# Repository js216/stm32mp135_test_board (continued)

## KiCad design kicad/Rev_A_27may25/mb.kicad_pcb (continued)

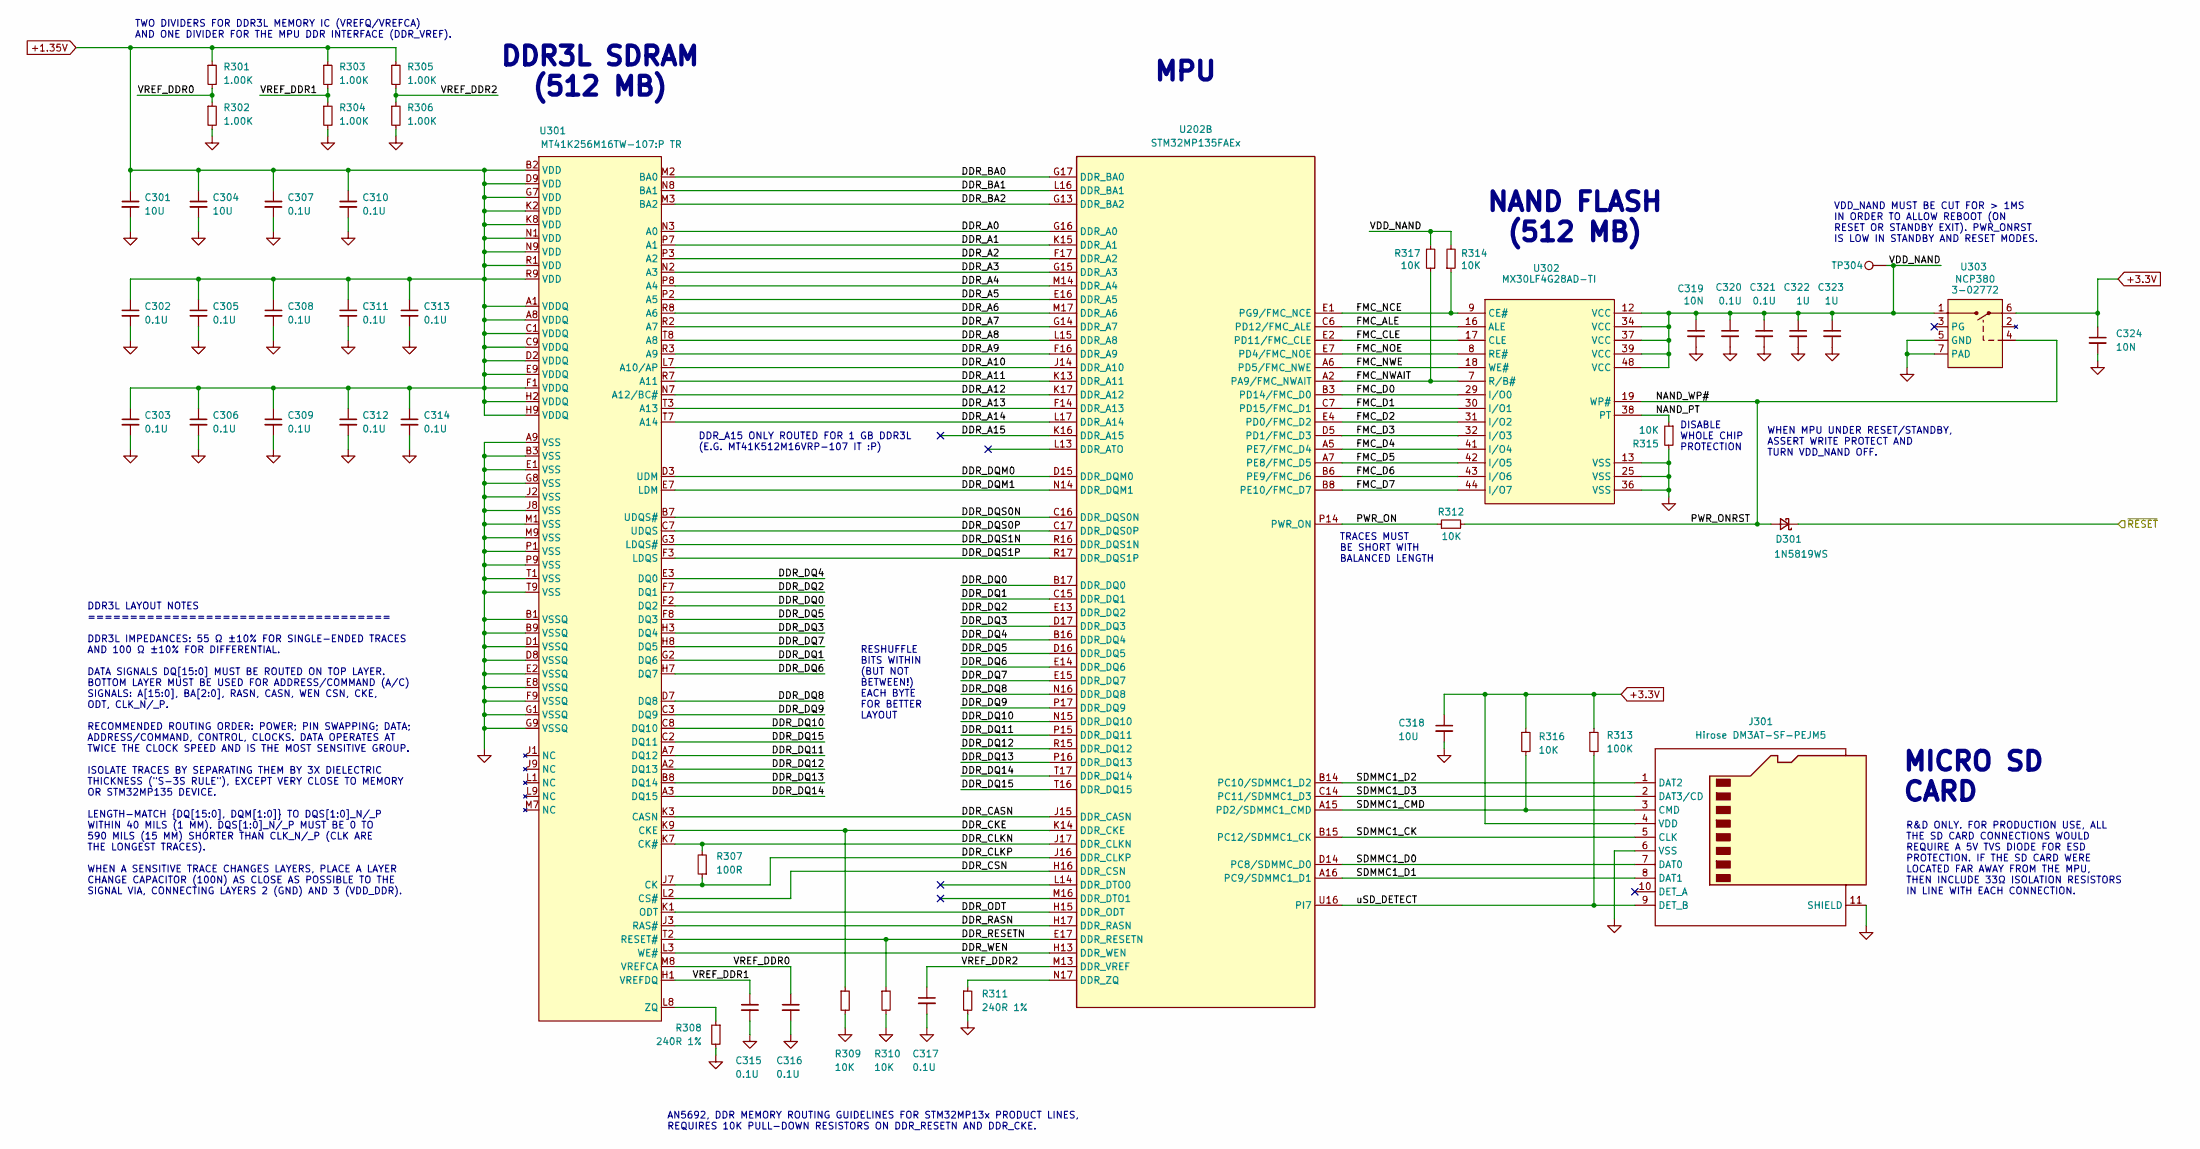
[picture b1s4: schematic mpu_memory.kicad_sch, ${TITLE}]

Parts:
C301, C304, C318: 10U; C_0402_1005Metric; JLCPCB C15525
C302, C303, C305, C306, C307, C308, C309, C310, C311, C312, C313, C314, C315, C316, C317, C320, C321: 0.1U; C_0402_1005Metric; JLCPCB C307331
C319, C324: 10N; C_0402_1005Metric; JLCPCB C15195
C322, C323: 1U; C_0402_1005Metric; JLCPCB C52923
D301: 1N5819WS; D_SOD-323; JLCPCB C191023
J301: Hirose DM3AT-SF-PEJM5; microSD_HC_Hirose_DM3AT-SF-PEJM5; JLCPCB C114218
R301, R302, R303, R304, R305, R306: 1.00K; R_0402_1005Metric; JLCPCB C11702
R307: 100R; R_0402_1005Metric; JLCPCB C25076
R308, R311: 240R 1%; R_0402_1005Metric; JLCPCB C25094
R309, R310, R312, R314, R315, R316, R317: 10K; R_0402_1005Metric; JLCPCB C25744
R313: 100K; R_0402_1005Metric; JLCPCB C25741
TP304: Keystone 5005 (red); TestPoint_Pad_D1.0mm
U202: STM32MP135FAEx; LFBGA-289_14x14mm_Layout17x17_P0.8mm; JLCPCB C7501745
U301: MT41K256M16TW-107:P TR; Micron_FBGA-96_8x14mm_Layout9x16_P0.8mm; JLCPCB C253882
U302: MX30LF4G28AD-TI; TSOP-I-48_18.4x12mm_P0.5mm; JLCPCB C2894351
U303: NCP380; DFN-6-1EP_2x2mm_P0.65mm_EP1x1.6mm; JLCPCB C145185

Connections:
+1.35V: C301.1, C302.1, C303.1, C304.1, C305.1, C306.1, C307.1, C308.1, C309.1, C310.1, C311.1, C312.1, C313.1, C314.1, R301.1, R303.1, R305.1, U301.A1 (VDDQ), U301.A8 (VDDQ), U301.B2 (VDD), U301.C1 (VDDQ), U301.C9 (VDDQ), U301.D2 (VDDQ), U301.D9 (VDD), U301.E9 (VDDQ), U301.F1 (VDDQ), U301.G7 (VDD), U301.H2 (VDDQ), U301.H9 (VDDQ), U301.K2 (VDD), U301.K8 (VDD), U301.N1 (VDD), U301.N9 (VDD), U301.R1 (VDD), U301.R9 (VDD); also elsewhere on the board
+3.3V: C318.1, C324.1, J301.4 (VDD), R313.1, R316.1, U303.6; also elsewhere on the board
/MPU Memory/DDR_A0: U202.G16 (DDR_A0), U301.N3 (A0)
/MPU Memory/DDR_A1: U202.K15 (DDR_A1), U301.P7 (A1)
/MPU Memory/DDR_A2: U202.F17 (DDR_A2), U301.P3 (A2)
/MPU Memory/DDR_A3: U202.G15 (DDR_A3), U301.N2 (A3)
/MPU Memory/DDR_A4: U202.M14 (DDR_A4), U301.P8 (A4)
/MPU Memory/DDR_A5: U202.E16 (DDR_A5), U301.P2 (A5)
/MPU Memory/DDR_A6: U202.M17 (DDR_A6), U301.R8 (A6)
/MPU Memory/DDR_A7: U202.G14 (DDR_A7), U301.R2 (A7)
/MPU Memory/DDR_A8: U202.L15 (DDR_A8), U301.T8 (A8)
/MPU Memory/DDR_A9: U202.F16 (DDR_A9), U301.R3 (A9)
/MPU Memory/DDR_A10: U202.J14 (DDR_A10), U301.L7 (A10/AP)
/MPU Memory/DDR_A11: U202.K13 (DDR_A11), U301.R7 (A11)
/MPU Memory/DDR_A12: U202.K17 (DDR_A12), U301.N7 (A12/BC#)
/MPU Memory/DDR_A13: U202.F14 (DDR_A13), U301.T3 (A13)
/MPU Memory/DDR_A14: U202.L17 (DDR_A14), U301.T7 (A14)
/MPU Memory/DDR_A15: U202.K16 (DDR_A15)
/MPU Memory/DDR_BA0: U202.G17 (DDR_BA0), U301.M2 (BA0)
/MPU Memory/DDR_BA1: U202.L16 (DDR_BA1), U301.N8 (BA1)
/MPU Memory/DDR_BA2: U202.G13 (DDR_BA2), U301.M3 (BA2)
/MPU Memory/DDR_CASN: U202.J15 (DDR_CASN), U301.K3 (CASN)
/MPU Memory/DDR_CKE: R309.1, U202.K14 (DDR_CKE), U301.K9 (CKE)
/MPU Memory/DDR_CLKN: R307.2, U202.J17 (DDR_CLKN), U301.K7 (CK#)
/MPU Memory/DDR_CLKP: R307.1, U202.J16 (DDR_CLKP), U301.J7 (CK)
/MPU Memory/DDR_CSN: U202.H16 (DDR_CSN), U301.L2 (CS#)
/MPU Memory/DDR_DQ0: U202.B17 (DDR_DQ0), U301.F2 (DQ2)
/MPU Memory/DDR_DQ1: U202.C15 (DDR_DQ1), U301.G2 (DQ6)
/MPU Memory/DDR_DQ2: U202.E13 (DDR_DQ2), U301.F7 (DQ1)
/MPU Memory/DDR_DQ3: U202.D17 (DDR_DQ3), U301.H3 (DQ4)
/MPU Memory/DDR_DQ4: U202.B16 (DDR_DQ4), U301.E3 (DQ0)
/MPU Memory/DDR_DQ5: U202.D16 (DDR_DQ5), U301.F8 (DQ3)
/MPU Memory/DDR_DQ6: U202.E14 (DDR_DQ6), U301.H7 (DQ7)
/MPU Memory/DDR_DQ7: U202.E15 (DDR_DQ7), U301.H8 (DQ5)
/MPU Memory/DDR_DQ8: U202.N16 (DDR_DQ8), U301.D7 (DQ8)
/MPU Memory/DDR_DQ9: U202.P17 (DDR_DQ9), U301.C3 (DQ9)
/MPU Memory/DDR_DQ10: U202.N15 (DDR_DQ10), U301.C8 (DQ10)
/MPU Memory/DDR_DQ11: U202.P15 (DDR_DQ11), U301.A7 (DQ12)
/MPU Memory/DDR_DQ12: U202.R15 (DDR_DQ12), U301.A2 (DQ13)
/MPU Memory/DDR_DQ13: U202.P16 (DDR_DQ13), U301.B8 (DQ14)
/MPU Memory/DDR_DQ14: U202.T17 (DDR_DQ14), U301.A3 (DQ15)
/MPU Memory/DDR_DQ15: U202.T16 (DDR_DQ15), U301.C2 (DQ11)
/MPU Memory/DDR_DQM0: U202.D15 (DDR_DQM0), U301.D3 (UDM)
/MPU Memory/DDR_DQM1: U202.N14 (DDR_DQM1), U301.E7 (LDM)
/MPU Memory/DDR_DQS0N: U202.C16 (DDR_DQS0N), U301.B7 (UDQS#)
/MPU Memory/DDR_DQS0P: U202.C17 (DDR_DQS0P), U301.C7 (UDQS)
/MPU Memory/DDR_DQS1N: U202.R16 (DDR_DQS1N), U301.G3 (LDQS#)
/MPU Memory/DDR_DQS1P: U202.R17 (DDR_DQS1P), U301.F3 (LDQS)
/MPU Memory/DDR_ODT: U202.H15 (DDR_ODT), U301.K1 (ODT)
/MPU Memory/DDR_RASN: U202.H17 (DDR_RASN), U301.J3 (RAS#)
/MPU Memory/DDR_RESETN: R310.1, U202.E17 (DDR_RESETN), U301.T2 (RESET#)
/MPU Memory/DDR_WEN: U202.H13 (DDR_WEN), U301.L3 (WE#)
/MPU Memory/FMC_ALE: U202.C6 (PD12/FMC_ALE), U302.16 (ALE)
/MPU Memory/FMC_CLE: U202.E2 (PD11/FMC_CLE), U302.17 (CLE)
/MPU Memory/FMC_D0: U202.B3 (PD14/FMC_D0), U302.29 (I/O0)
/MPU Memory/FMC_D1: U202.C7 (PD15/FMC_D1), U302.30 (I/O1)
/MPU Memory/FMC_D2: U202.E4 (PD0/FMC_D2), U302.31 (I/O2)
/MPU Memory/FMC_D3: U202.D5 (PD1/FMC_D3), U302.32 (I/O3)
/MPU Memory/FMC_D4: U202.A5 (PE7/FMC_D4), U302.41 (I/O4)
/MPU Memory/FMC_D5: U202.A7 (PE8/FMC_D5), U302.42 (I/O5)
/MPU Memory/FMC_D6: U202.B6 (PE9/FMC_D6), U302.43 (I/O6)
/MPU Memory/FMC_D7: U202.B8 (PE10/FMC_D7), U302.44 (I/O7)
/MPU Memory/FMC_NCE: R314.1, U202.E1 (PG9/FMC_NCE), U302.9 (CE#)
/MPU Memory/FMC_NOE: U202.E7 (PD4/FMC_NOE), U302.8 (RE#)
/MPU Memory/FMC_NWAIT: R317.1, U202.A2 (PA9/FMC_NWAIT), U302.7 (R/B#)
/MPU Memory/FMC_NWE: U202.A6 (PD5/FMC_NWE), U302.18 (WE#)
/MPU Memory/NAND_PT: R315.1, U302.38 (PT)
/MPU Memory/NAND_WP#: D301.2 (A), R312.2, U302.19 (WP#), U303.4
/MPU Memory/PWR_ON: R312.1, U202.P14 (PWR_ON)
/MPU Memory/SDMMC1_CK: J301.5 (CLK), U202.B15 (PC12/SDMMC1_CK)
/MPU Memory/SDMMC1_CMD: J301.3 (CMD), R316.2, U202.A15 (PD2/SDMMC1_CMD)
/MPU Memory/SDMMC1_D0: J301.7 (DAT0), U202.D14 (PC8/SDMMC_D0)
/MPU Memory/SDMMC1_D1: J301.8 (DAT1), U202.A16 (PC9/SDMMC1_D1)
/MPU Memory/SDMMC1_D2: J301.1 (DAT2), U202.B14 (PC10/SDMMC1_D2)
/MPU Memory/SDMMC1_D3: J301.2 (DAT3/CD), U202.C14 (PC11/SDMMC1_D3)
/MPU Memory/VDD_NAND: C319.1, C320.1, C321.1, C322.1, C323.1, R314.2, R317.2, TP304.1, U302.12 (VCC), U302.34 (VCC), U302.37 (VCC), U302.39 (VCC), U302.48 (VCC), U303.1
/MPU Memory/VREF_DDR0: C316.1, R301.2, R302.1, U301.M8 (VREFCA)
/MPU Memory/VREF_DDR1: C315.1, R303.2, R304.1, U301.H1 (VREFDQ)
/MPU Memory/VREF_DDR2: C317.1, R305.2, R306.1, U202.M13 (DDR_VREF)
/MPU Memory/uSD_DETECT: J301.9 (DET_B), R313.2, U202.U16 (PI7)
/~RESET: D301.1 (K); also elsewhere on the board
GND: C301.2, C302.2, C303.2, C304.2, C305.2, C306.2, C307.2, C308.2, C309.2, C310.2, C311.2, C312.2, C313.2, C314.2, C315.2, C316.2, C317.2, C318.2, C319.2, C320.2, C321.2, C322.2, C323.2, C324.2, J301.6 (VSS), J301.11 (SHIELD), R302.2, R304.2, R306.2, R308.2, R309.2, R310.2, R311.2, R315.2, U301.A9 (VSS), U301.B1 (VSSQ), U301.B3 (VSS), U301.B9 (VSSQ), U301.D1 (VSSQ), U301.D8 (VSSQ), U301.E1 (VSS), U301.E2 (VSSQ), U301.E8 (VSSQ), U301.F9 (VSSQ), U301.G1 (VSSQ), U301.G8 (VSS), U301.G9 (VSSQ), U301.J2 (VSS), U301.J8 (VSS), U301.M1 (VSS), U301.M9 (VSS), U301.P1 (VSS), U301.P9 (VSS), U301.T1 (VSS), U301.T9 (VSS), U302.13 (VSS), U302.25 (VSS), U302.36 (VSS), U303.5 (GND), U303.7 (PAD); also elsewhere on the board
unnamed: R311.1, U202.N17 (DDR_ZQ)
unnamed: R308.1, U301.L8 (ZQ)

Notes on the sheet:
MICRO SD CARD
DDR3L SDRAM (512 MB)
VDD_NAND MUST BE CUT FOR > 1MS IN ORDER TO ALLOW REBOOT (ON RESET OR STANDBY EXIT). PWR_ONRST IS LOW IN STANDBY AND RESET MODES.
DDR_A15 ONLY ROUTED FOR 1 GB DDR3L (E.G. MT41K512M16VRP-107 IT :P)
TWO DIVIDERS FOR DDR3L MEMORY IC (VREFQ/VREFCA) AND ONE DIVIDER FOR THE MPU DDR INTERFACE (DDR_VREF).
MPU
AN5692, DDR MEMORY ROUTING GUIDELINES FOR STM32MP13x PRODUCT LINES, REQUIRES 10K PULL-DOWN RESISTORS ON DDR_RESETN AND DDR_CKE.
TRACES MUST BE SHORT WITH BALANCED LENGTH
WHEN MPU UNDER RESET/STANDBY, ASSERT WRITE PROTECT AND TURN VDD_NAND OFF.
RESHUFFLE BITS WITHIN (BUT NOT BETWEEN!) EACH BYTE FOR BETTER LAYOUT
NAND FLASH (512 MB)
DISABLE WHOLE CHIP PROTECTION
DDR3L LAYOUT NOTES ==================================== DDR3L IMPEDANCES: 55 Ω ±10% FOR SINGLE-ENDED TRACES AND 100 Ω ±10% FOR DIFFERENTIAL. DATA SIGNALS DQ[15:0] MUST BE ROUTED ON TOP LAYER. BOTTOM LAYER MUST BE USED FOR ADDRESS/COMMAND (A/C) SIGNALS: A[15:0], BA[2:0], RASN, CASN, WEN CSN, CKE, OD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
R&D ONLY. FOR PRODUCTION USE, ALL THE SD CARD CONNECTIONS WOULD REQUIRE A 5V TVS DIODE FOR ESD PROTECTION. IF THE SD CARD WERE LOCATED FAR AWAY FROM THE MPU, THEN INCLUDE 33Ω ISOLATION RESISTORS IN LINE WITH EACH CONNECTION.

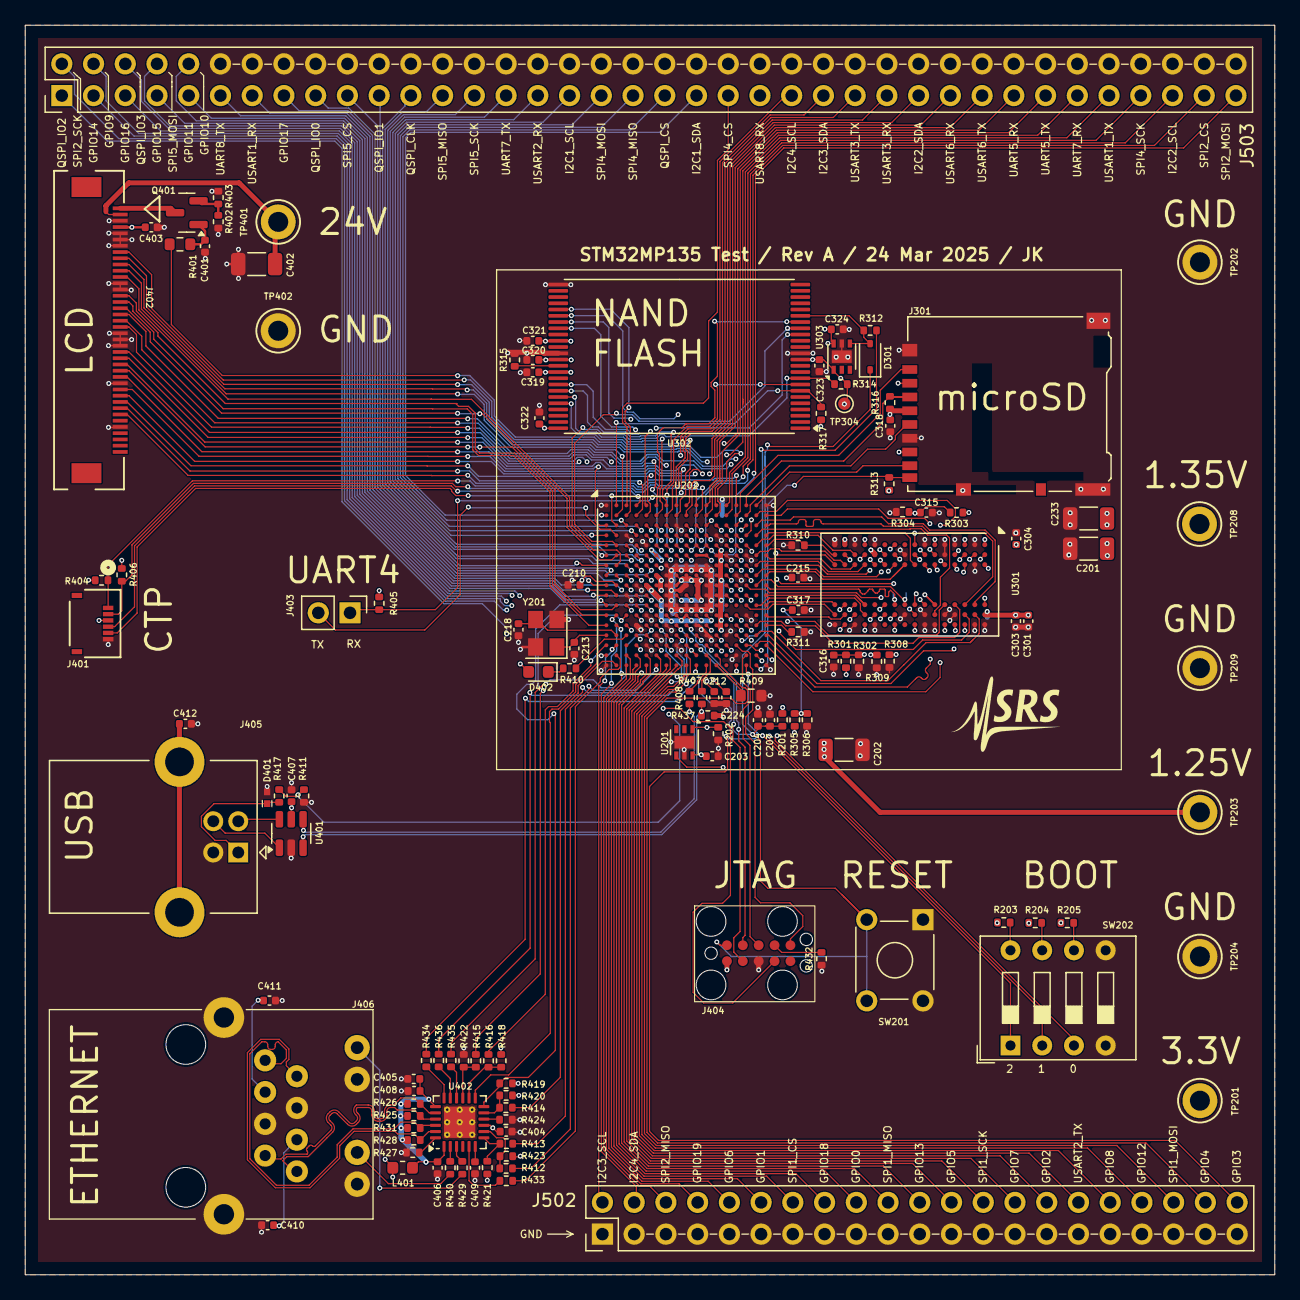
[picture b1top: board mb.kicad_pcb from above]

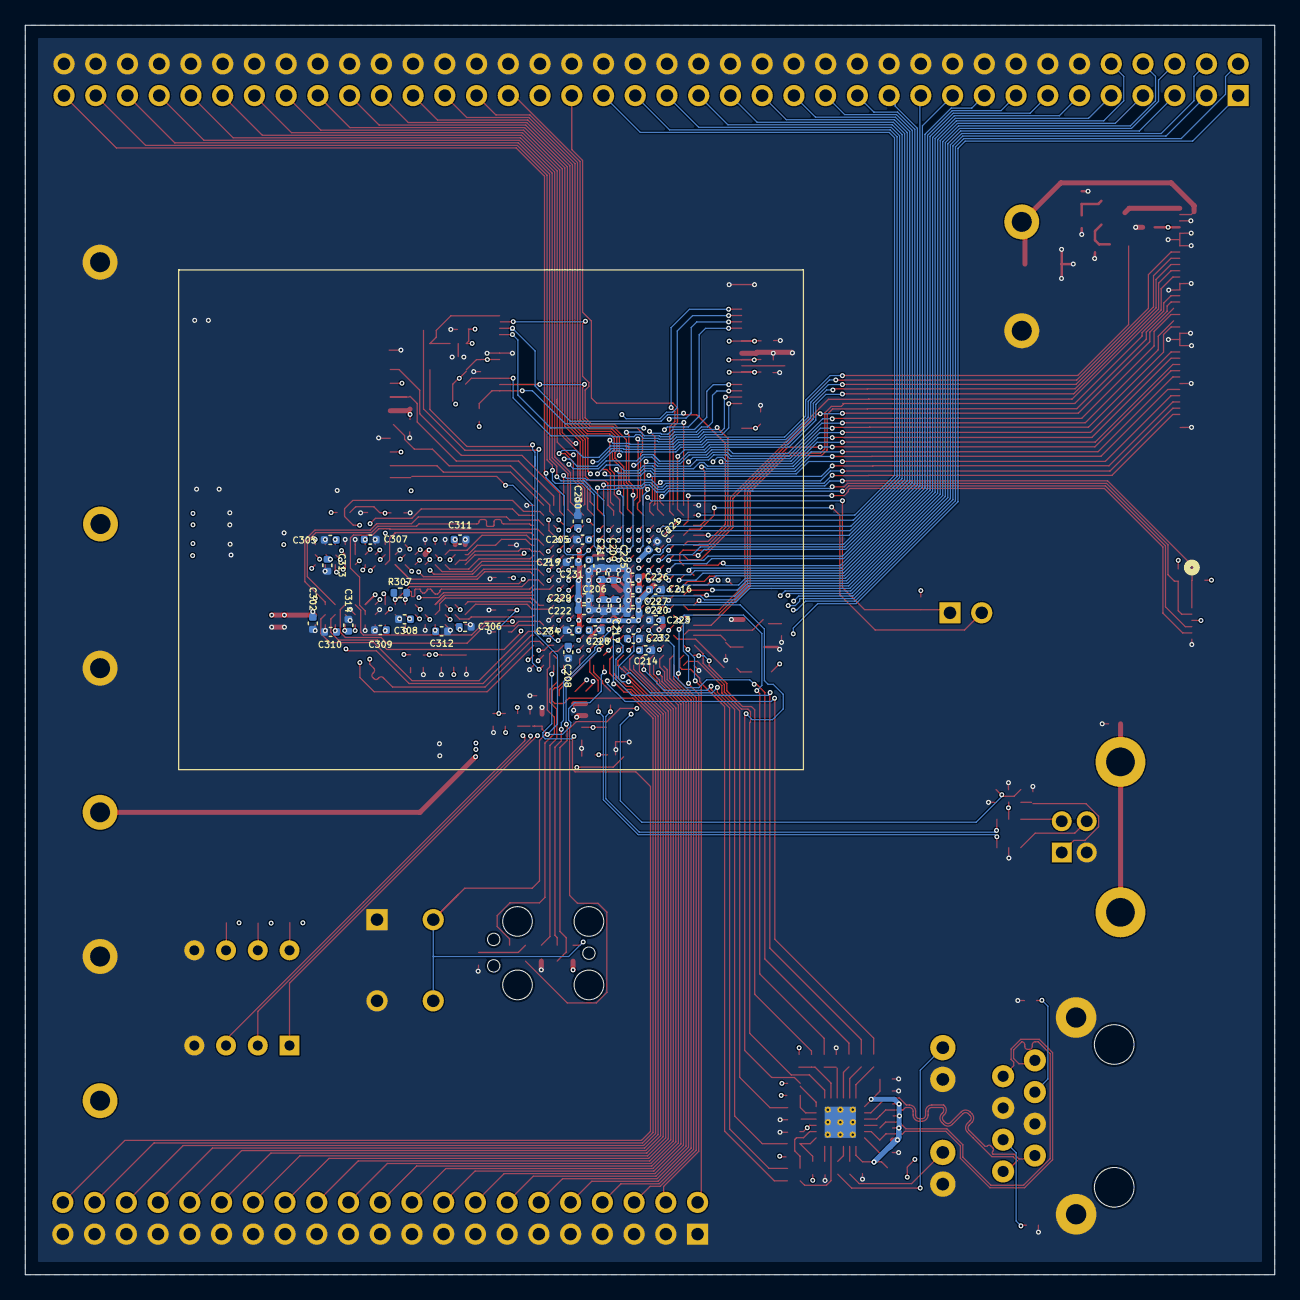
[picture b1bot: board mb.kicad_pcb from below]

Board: 6 copper layers, 100.0 x 100.0 mm, 162 parts (34 on the bottom side), 243 nets.

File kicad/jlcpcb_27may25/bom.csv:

"Reference","Value","Qty","JLCPCB"
"C201","100U","1","C15008"
"C202","100U","1","C15008"
"C203","10N","1","C15195"
"C204","10N","1","C15195"
"C205","1U","1","C52923"
"C206","1U","1","C52923"
"C207","1U","1","C52923"
"C208","1U","1","C52923"
"C209","1U","1","C52923"
"C210","1U","1","C52923"
"C211","1U","1","C52923"
"C212","1U","1","C52923"
"C213","10P","1","C32949"
"C214","1U","1","C52923"
"C215","1U","1","C52923"
"C216","1U","1","C52923"
"C217","1U","1","C52923"
"C218","10P","1","C32949"
"C219","1U","1","C52923"
"C220","1U","1","C52923"
"C221","1U","1","C52923"
"C222","1nF","1","C1523"
"C223","1U","1","C52923"
"C224","2.2U","1"," C12530"
"C225","1U","1","C52923"
"C226","1nF","1","C1523"
"C227","1U","1","C52923"
"C228","2.2U","1"," C12530"
"C229","1U","1","C52923"
"C230","1U","1","C52923"
"C231","0.1U","1","C307331"
"C232","1U","1","C52923"
"C233","100U","1","C15008"
"C234","1U","1","C52923"
"C301","10U","1","C15525"
"C302","0.1U","1","C307331"
"C303","0.1U","1","C307331"
"C304","10U","1","C15525"
"C305","0.1U","1","C307331"
"C306","0.1U","1","C307331"
"C307","0.1U","1","C307331"
"C308","0.1U","1","C307331"
"C309","0.1U","1","C307331"
"C310","0.1U","1","C307331"
"C311","0.1U","1","C307331"
"C312","0.1U","1","C307331"
"C313","0.1U","1","C307331"
"C314","0.1U","1","C307331"
"C315","0.1U","1","C307331"
"C316","0.1U","1","C307331"
"C317","0.1U","1","C307331"
"C318","10U","1","C15525"
"C319","10N","1","C15195"
"C320","0.1U","1","C307331"
"C321","0.1U","1","C307331"
"C322","1U","1","C52923"
"C323","1U","1","C52923"
"C324","10N","1","C15195"
"C401","4.7U","1","C23733"
"C402","4.7U 50V","1","C29823"
"C403","0.1U","1","C307331"
"C404","0.1U","1","C307331"
"C405","10U","1","C15525"
"C406","0.1U","1","C307331"
"C407","0.1U","1","C307331"
"C408","0.1U","1","C307331"
"C409","1U","1","C52923"
"C410","0.1U","1","C307331"
"C411","0.1U","1","C307331"
"C412","1nF","1","C1523"
"D301","1N5819WS","1","C191023"
"D401","6V TVS","1","C472589"
"D402","Red","1","C2286"
"J301","Hirose DM3AT-SF-PEJM5","1","C114218"
"J401","Conn_01x08","1","C5213748"
"J402","Molex 541044031","1","C164172"
"J403","Header","1",""
"J405","USB_B","1",""
"J406","J1011F21PNL","1",""
"J502","Conn_02x21_Odd_Even","1",""
"J503","Conn_02x38_Odd_Even","1",""
"L401","600R @ 100MHz","1","C1002"
"Q401"," MMBT5551","1","C2145"
"R201","10K","1","C25744"
"R202","10K","1","C25744"
"R203","1.00K","1","C11702"
"R204","1.00K","1","C11702"
"R205","1.00K","1","C11702"
"R301","1.00K","1","C11702"
"R302","1.00K","1","C11702"
"R303","1.00K","1","C11702"
"R304","1.00K","1","C11702"
"R305","1.00K","1","C11702"
"R306","1.00K","1","C11702"
"R307","100R","1","C25076"
"R308","240R 1%","1","C25094"
"R309","10K","1","C25744"
"R310","10K","1","C25744"
"R311","240R 1%","1","C25094"
"R312","10K","1","C25744"
"R313","100K","1","C25741"
"R314","10K","1","C25744"
"R315","10K","1","C25744"
"R316","10K","1","C25744"
"R317","10K","1","C25744"
"R401","270","1","C22966"
"R402","100R","1","C25076"
"R403","100R","1","C25076"
"R404","10K","1","C25744"
"R405","10K","1","C25744"
"R406","10K","1","C25744"
"R407","30.1","1","C67234"
"R408","30.1","1","C67234"
"R409","3.00K","1","C4211"
"R410","330","1","C25104"
"R411","10K","1","C25744"
"R412","33","1","C25105"
"R413","33","1","C25105"
"R414","33","1","C25105"
"R415","0","1","C17168"
"R416","0","1","C17168"
"R417","10K","1","C25744"
"R418","10K","1","C25744"
"R419","1.5K","1","C25867"
"R420","10K","1","C25744"
"R421","10K","1","C25744"
"R422","10K","1","C25744"
"R423","10K","1","C25744"
"R424","10K","1","C25744"
"R425","49.9","1","C25120"
"R426","49.9","1","C25120"
"R427","12.1K","1","C25852"
"R428","49.9","1","C25120"
"R429","1.00K","1","C11702"
"R430","1.00K","1","C11702"
"R431","49.9","1","C25120"
"R432","10K","1","C25744"
"R433","33","1","C25105"
"R434","0","1","C17168"
"R435","0","1","C17168"
"R436","0","1","C17168"
"R437","1.5K","1","C25867"
"SW201","Omron B3F-1052","1",""
"SW202","SW_DIP_x04","1",""
"U201","NCP380","1","C145185"
"U202","STM32MP135FAEx","1","C7501745"
"U301","MT41K256M16TW-107:P TR","1","C253882 "
"U302","MX30LF4G28AD-TI","1","C2894351"
"U303","NCP380","1","C145185"
"U401","TPD2S017","1","C880115"
"U402","LAN8742A-CZ-TR","1","C621424"
"Y201","24 MHz","1","C70571"

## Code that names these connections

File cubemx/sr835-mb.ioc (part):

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Mcu.Name=STM32MP135FAEx
Mcu.Package=LFBGA289
Mcu.UserName=STM32MP135FAEx
PA0.GPIOParameters=PinAttribute
PA0.PinAttribute=Application
PA0.Signal=S_TIM2_CH1_ETR
PA1.GPIOParameters=GPIO_Label,PinAttribute
PA1.GPIO_Label=uSD_DETECT
PA1.PinAttribute=Free
PA1.Signal=GPIO_Input
PA10.GPIOParameters=GPIO_Label,PinAttribute
PA10.GPIO_Label=GPIO3
PA10.PinAttribute=Free
PA10.Signal=GPIO_Output
PA11.GPIOParameters=PinAttribute
PA11.Mode=ETH Clock Output (PHY without Quartz)
PA11.PinAttribute=Application
PA11.Signal=ETH1_CLK
PA12.GPIOParameters=PinAttribute
PA12.Mode=RGB565
PA12.PinAttribute=Application
PA12.Signal=LTDC_G6
PA13.GPIOParameters=GPIO_Label,PinAttribute
PA13.GPIO_Label=LED_RED
PA13.PinAttribute=Free
PA13.Signal=GPIO_Output
PA14.GPIOParameters=GPIO_Label,PinAttribute
PA14.GPIO_Label=GPIO4
PA14.PinAttribute=Free
PA14.Signal=GPIO_Output
PA15.GPIOParameters=PinAttribute
PA15.Mode=RGB565
PA15.PinAttribute=Application
PA15.Signal=LTDC_G7
PA2.GPIOParameters=PinAttribute
PA2.Mode=IN1-Single-Ended
PA2.PinAttribute=Application
PA2.Signal=ADC1_INP1
PA3.GPIOParameters=PinAttribute
PA3.Mode=Full_Duplex_Master
PA3.PinAttribute=Application
PA3.Signal=SPI1_MOSI
PA4.GPIOParameters=GPIO_Label,PinAttribute
PA4.GPIO_Label=GPIO0
PA4.PinAttribute=Free
PA4.Signal=GPIO_Output
PA5.GPIOParameters=GPIO_Label,PinAttribute
PA5.GPIO_Label=GPIO1
PA5.PinAttribute=Free
PA5.Signal=GPIO_Output
PA6.GPIOParameters=PinAttribute
PA6.Mode=CTS_RTS
PA6.PinAttribute=Application
PA6.Signal=UART4_RTS
PA7.GPIOParameters=PinAttribute
PA7.Mode=RMII (Reduced MII)
PA7.PinAttribute=Application
PA7.Signal=ETH1_CRS_DV
PA8.GPIOParameters=PinAttribute
PA8.Mode=I2C
PA8.PinAttribute=Application
PA8.Signal=I2C4_SDA
PA9.GPIOParameters=PinAttribute
PA9.PinAttribute=Application
PA9.Signal=FMC_NWAIT
PB0.GPIOParameters=PinAttribute
PB0.Mode=CTS_RTS
PB0.PinAttribute=Application
PB0.Signal=UART4_CTS
PB1.GPIOParameters=PinAttribute
PB1.Mode=Full_Duplex_Master
PB1.PinAttribute=Application
PB1.Signal=SPI1_SCK
PB10.GPIOParameters=PinAttribute
PB10.Mode=Asynchronous
PB10.PinAttribute=Application
PB10.Signal=USART3_TX
PB11.GPIOParameters=PinAttribute
PB11.Mode=RMII (Reduced MII)
PB11.PinAttribute=Application
PB11.Signal=ETH1_TX_EN
PB12.GPIOParameters=PinAttribute
PB12.Mode=RGB565
PB12.PinAttribute=Application
PB12.Signal=LTDC_R3
PB13.GPIOParameters=PinAttribute
PB13.Mode=NSS_Signal_Hard_Output
PB13.PinAttribute=Application
PB13.Signal=SPI2_NSS
PB14.GPIOParameters=PinAttribute
PB14.Mode=Asynchronous
PB14.PinAttribute=Application
PB14.Signal=USART1_TX
PB15.GPIOParameters=PinAttribute
PB15.Mode=Output Compare3 CH3N
PB15.PinAttribute=Application
PB15.Signal=TIM1_CH3N
PB2.GPIOParameters=PinAttribute
PB2.Mode=RGB565
PB2.PinAttribute=Application
PB2.Signal=LTDC_B4
PB3.GPIOParameters=PinAttribute
PB3.Mode=Asynchronous
PB3.PinAttribute=Application
PB3.Signal=UART7_RX
PB4.GPIOParameters=PinAttribute
PB4.Mode=Full_Duplex_Master
PB4.PinAttribute=Application
PB4.Signal=SPI4_SCK
PB5.GPIOParameters=PinAttribute
PB5.Mode=Asynchronous
PB5.PinAttribute=Application
PB5.Signal=UART5_RX
PB6.GPIOParameters=PinAttribute
PB6.Mode=RGB565
PB6.PinAttribute=Application
PB6.Signal=LTDC_B7
PB7.GPIOParameters=GPIO_Label,PinAttribute
PB7.GPIO_Label=CTP_RST
PB7.PinAttribute=Free
PB7.Signal=GPIO_Output
PB8.GPIOParameters=PinAttribute
PB8.Mode=I2C
PB8.PinAttribute=Application
PB8.Signal=I2C1_SCL
PB9.GPIOParameters=PinAttribute
PB9.Mode=Asynchronous
PB9.PinAttribute=Application
PB9.Signal=UART5_TX
PC0.GPIOParameters=GPIO_Label,PinAttribute
PC0.GPIO_Label=GPIO6
PC0.PinAttribute=Free
PC0.Signal=GPIO_Output
PC1.GPIOParameters=GPIO_Label,PinAttribute
PC1.GPIO_Label=GPIO7
PC1.PinAttribute=Free
PC1.Signal=GPIO_Output
PC10.GPIOParameters=PinAttribute
PC10.Mode=SD_4_bits_Wide_bus
PC10.PinAttribute=Application
PC10.Signal=SDMMC1_D2
PC11.GPIOParameters=PinAttribute
PC11.Mode=SD_4_bits_Wide_bus
PC11.PinAttribute=Application
PC11.Signal=SDMMC1_D3
PC12.GPIOParameters=PinAttribute
PC12.Mode=SD_4_bits_Wide_bus
PC12.PinAttribute=Application
PC12.Signal=SDMMC1_CK
PC13.GPIOParameters=GPIO_Label,PinAttribute
PC13.GPIO_Label=GPIO9
PC13.PinAttribute=Free
PC13.Signal=GPIO_Output
PC14-OSC32_IN.GPIOParameters=GPIO_Label,PinAttribute
PC14-OSC32_IN.GPIO_Label=GPIO10
PC14-OSC32_IN.PinAttribute=Free
PC14-OSC32_IN.Signal=GPIO_Output
PC15-OSC32_OUT.GPIOParameters=GPIO_Label,PinAttribute
PC15-OSC32_OUT.GPIO_Label=GPIO11
PC15-OSC32_OUT.PinAttribute=Free
PC15-OSC32_OUT.Signal=GPIO_Output
PC2.GPIOParameters=GPIO_Label,PinAttribute
PC2.GPIO_Label=GPIO8
PC2.PinAttribute=Free
PC2.Signal=GPIO_Output
PC3.GPIOParameters=PinAttribute
PC3.Mode=Full_Duplex_Master
PC3.PinAttribute=Application
PC3.Signal=SPI1_MISO
PC4.GPIOParameters=PinAttribute
PC4.Mode=RMII (Reduced MII)
PC4.PinAttribute=Application
PC4.Signal=ETH1_RXD0
PC5.GPIOParameters=PinAttribute
PC5.Mode=RMII (Reduced MII)
PC5.PinAttribute=Application
PC5.Signal=ETH1_RXD1
PC6.GPIOParameters=PinAttribute
PC6.Mode=Asynchronous
PC6.PinAttribute=Application
PC6.Signal=USART6_TX
PC7.GPIOParameters=PinAttribute
PC7.Mode=Asynchronous
PC7.PinAttribute=Application
PC7.Signal=USART6_RX
PC8.GPIOParameters=PinAttribute
PC8.Mode=SD_4_bits_Wide_bus
PC8.PinAttribute=Application
PC8.Signal=SDMMC1_D0
PC9.GPIOParameters=PinAttribute
PC9.Mode=SD_4_bits_Wide_bus
PC9.PinAttribute=Application
PC9.Signal=SDMMC1_D1
PD0.GPIOParameters=PinAttribute
PD0.PinAttribute=Application
PD0.Signal=FMC_D2_DA2
PD1.GPIOParameters=PinAttribute
PD1.PinAttribute=Application
PD1.Signal=FMC_D3_DA3
PD10.GPIOParameters=PinAttribute
PD10.Mode=NSS_Signal_Hard_Output
PD10.PinAttribute=Application
PD10.Signal=SPI4_NSS
PD11.GPIOParameters=PinAttribute
PD11.PinAttribute=Application
PD11.Signal=FMC_A16_CLE
PD12.GPIOParameters=PinAttribute
PD12.PinAttribute=Application
PD12.Signal=FMC_A17_ALE
PD13.GPIOParameters=PinAttribute
PD13.Mode=Asynchronous
PD13.PinAttribute=Application
PD13.Signal=USART1_RX
PD14.GPIOParameters=PinAttribute
PD14.PinAttribute=Application
PD14.Signal=FMC_D0_DA0
PD15.GPIOParameters=PinAttribute
PD15.PinAttribute=Application
PD15.Signal=FMC_D1_DA1
PD2.GPIOParameters=PinAttribute
PD2.Mode=SD_4_bits_Wide_bus
PD2.PinAttribute=Application
PD2.Signal=SDMMC1_CMD
PD3.GPIOParameters=PinAttribute
PD3.Mode=I2C
PD3.PinAttribute=Application
PD3.Signal=I2C1_SDA
PD4.GPIOParameters=PinAttribute
PD4.PinAttribute=Application
PD4.Signal=FMC_NOE
PD5.GPIOParameters=PinAttribute
PD5.PinAttribute=Application
PD5.Signal=FMC_NWE
PD6.GPIOParameters=PinAttribute
PD6.Mode=Asynchronous
PD6.PinAttribute=Application
PD6.Signal=UART4_TX
PD7.GPIOParameters=PinAttribute
PD7.Mode=Single Bank 1
PD7.PinAttribute=Application
PD7.Signal=QUADSPI_BK1_IO2
PD8.GPIOParameters=PinAttribute
PD8.Mode=Asynchronous
PD8.PinAttribute=Application
PD8.Signal=UART4_RX
PD9.GPIOParameters=PinAttribute
PD9.Mode=RGB565
PD9.PinAttribute=Application
PD9.Signal=LTDC_CLK
PE0.GPIOParameters=PinAttribute
PE0.Mode=Asynchronous
PE0.PinAttribute=Application
PE0.Signal=UART8_RX
PE1.GPIOParameters=PinAttribute
PE1.Mode=RGB565
PE1.PinAttribute=Application
PE1.Signal=LTDC_HSYNC
PE10.GPIOParameters=PinAttribute
PE10.PinAttribute=Application
PE10.Signal=FMC_D7_DA7
PE11.GPIOParameters=PinAttribute
PE11.Mode=Full_Duplex_Master
PE11.PinAttribute=Application
PE11.Signal=SPI4_MOSI
PE12.GPIOParameters=PinAttribute
PE12.Mode=RGB565
PE12.PinAttribute=Application
PE12.Signal=LTDC_VSYNC
PE13.GPIOParameters=PinAttribute
PE13.Mode=Full_Duplex_Master
PE13.PinAttribute=Application
PE13.Signal=SPI4_MISO
PE14.GPIOParameters=PinAttribute
PE14.Mode=Single Bank 1
PE14.PinAttribute=Application
PE14.Signal=QUADSPI_BK1_NCS
PE15.GPIOParameters=PinAttribute
PE15.Mode=I2C
PE15.PinAttribute=Application
PE15.Signal=I2C4_SCL
PE2.GPIOParameters=PinAttribute
PE2.Mode=Full_Duplex_Master
PE2.PinAttribute=Application
PE2.Signal=SPI5_MOSI
PE3.GPIOParameters=PinAttribute
PE3.Mode=RGB565
PE3.PinAttribute=Application
PE3.Signal=LTDC_R4
PE4.GPIOParameters=PinAttribute
PE4.Mode=Asynchronous
PE4.PinAttribute=Application
PE4.Signal=UART8_TX
PE5.GPIOParameters=GPIO_Label,PinAttribute
PE5.GPIO_Label=GPIO12
PE5.PinAttribute=Free
PE5.Signal=GPIO_Output
PE6.GPIOParameters=PinAttribute
PE6.Mode=RGB565
PE6.PinAttribute=Application
PE6.Signal=LTDC_G3
PE7.GPIOParameters=PinAttribute
PE7.PinAttribute=Application
PE7.Signal=FMC_D4_DA4
PE8.GPIOParameters=PinAttribute
PE8.PinAttribute=Application
PE8.Signal=FMC_D5_DA5
PE9.GPIOParameters=PinAttribute
PE9.PinAttribute=Application
PE9.Signal=FMC_D6_DA6
PF0.GPIOParameters=PinAttribute
PF0.Mode=RGB565
PF0.PinAttribute=Application
PF0.Signal=LTDC_R6
PF1.GPIOParameters=PinAttribute
PF1.Mode=I2C
PF1.PinAttribute=Application
PF1.Signal=I2C2_SDA
PF10.GPIOParameters=PinAttribute
PF10.Mode=Single Bank 1
PF10.PinAttribute=Application
PF10.Signal=QUADSPI_CLK
PF11.GPIOParameters=GPIO_Label,PinAttribute
PF11.GPIO_Label=GPIO13
PF11.PinAttribute=Free
PF11.Signal=GPIO_Output
PF12.GPIOParameters=PinAttribute
PF12.Mode=NSS_Signal_Hard_Output
PF12.PinAttribute=Application
PF12.Signal=SPI1_NSS
PF13.GPIOParameters=PinAttribute
PF13.Mode=Asynchronous

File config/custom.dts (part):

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						 <STM32_PINMUX('G', 14, AF11)>, /* ETH_RMII_TXD1 */
						 <STM32_PINMUX('B', 11, AF11)>, /* ETH_RMII_TX_EN */
						 <STM32_PINMUX('A', 11, AF11)>, /* ETH_RMII_ETHCK */
						 <STM32_PINMUX('G', 3, AF11)>, /* ETH_MDIO */
						 <STM32_PINMUX('G', 2, AF11)>; /* ETH_MDC */
					bias-disable;
					drive-push-pull;
					slew-rate = <1>;
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						 <STM32_PINMUX('G', 14, ANALOG)>, /* ETH_RMII_TXD1 */
						 <STM32_PINMUX('B', 11, ANALOG)>, /* ETH_RMII_TX_EN */
						 <STM32_PINMUX('A', 11, ANALOG)>, /* ETH_RMII_ETHCK */
						 <STM32_PINMUX('A', 2, ANALOG)>, /* ETH_MDIO */
						 <STM32_PINMUX('G', 2, ANALOG)>, /* ETH_MDC */
						 <STM32_PINMUX('C', 4, ANALOG)>, /* ETH_RMII_RXD0 */
						 <STM32_PINMUX('C', 5, ANALOG)>, /* ETH_RMII_RXD1 */
						 <STM32_PINMUX('C', 1, ANALOG)>; /* ETH_RMII_CRS_DV */
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						 <STM32_PINMUX('G', 11, AF10)>, /* ETH_RMII_TXD1 */
						 <STM32_PINMUX('G', 8, AF13)>, /* ETH_RMII_ETHCK */
						 <STM32_PINMUX('F', 6, AF11)>, /* ETH_RMII_TX_EN */
						 <STM32_PINMUX('B', 2, AF11)>, /* ETH_MDIO */
						 <STM32_PINMUX('G', 5, AF10)>; /* ETH_MDC */
					bias-disable;
					drive-push-pull;
					slew-rate = <1>;
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						 <STM32_PINMUX('G', 11, ANALOG)>, /* ETH_RMII_TXD1 */
						 <STM32_PINMUX('G', 8, ANALOG)>, /* ETH_RMII_ETHCK */
						 <STM32_PINMUX('F', 6, ANALOG)>, /* ETH_RMII_TX_EN */
						 <STM32_PINMUX('B', 2, ANALOG)>, /* ETH_MDIO */
						 <STM32_PINMUX('G', 5, ANALOG)>, /* ETH_MDC */
						 <STM32_PINMUX('F', 4, ANALOG)>, /* ETH_RMII_RXD0 */
						 <STM32_PINMUX('E', 2, ANALOG)>, /* ETH_RMII_RXD1 */
						 <STM32_PINMUX('A', 12, ANALOG)>; /* ETH_RMII_CRS_DV */
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
			i2c1_pins_a: i2c1-0 {
				pins {
					pinmux = <STM32_PINMUX('D', 12, AF5)>, /* I2C1_SCL */
						 <STM32_PINMUX('E', 8, AF5)>; /* I2C1_SDA */
					bias-disable;
					drive-open-drain;
					slew-rate = <0>;
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
			i2c1_sleep_pins_a: i2c1-sleep-0 {
				pins {
					pinmux = <STM32_PINMUX('D', 12, ANALOG)>, /* I2C1_SCL */
						 <STM32_PINMUX('E', 8, ANALOG)>; /* I2C1_SDA */
				};
			};

			i2c4_pins_a: i2c4-0 {
				pins {
					pinmux = <STM32_PINMUX('E', 15, AF6)>, /* I2C4_SCL */
						 <STM32_PINMUX('B', 9, AF6)>; /* I2C4_SDA */
					bias-disable;
					drive-open-drain;
					slew-rate = <0>;
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
			sdmmc1_b4_pins_a: sdmmc1-b4-0 {
				pins {
					pinmux = <STM32_PINMUX('C', 8, AF12)>, /* SDMMC1_D0 */
						 <STM32_PINMUX('C', 9, AF12)>, /* SDMMC1_D1 */
						 <STM32_PINMUX('C', 10, AF12)>, /* SDMMC1_D2 */
						 <STM32_PINMUX('C', 11, AF12)>, /* SDMMC1_D3 */
						 <STM32_PINMUX('D', 2, AF12)>; /* SDMMC1_CMD */
					slew-rate = <1>;
					drive-push-pull;
					bias-pull-up;
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
			sdmmc1_b4_od_pins_a: sdmmc1-b4-od-0 {
				pins1 {
					pinmux = <STM32_PINMUX('C', 8, AF12)>, /* SDMMC1_D0 */
						 <STM32_PINMUX('C', 9, AF12)>, /* SDMMC1_D1 */
						 <STM32_PINMUX('C', 10, AF12)>, /* SDMMC1_D2 */
						 <STM32_PINMUX('C', 11, AF12)>; /* SDMMC1_D3 */
					slew-rate = <1>;
					drive-push-pull;
					bias-pull-up;
				};
				pins2 {
					pinmux = <STM32_PINMUX('D', 2, AF12)>; /* SDMMC1_CMD */
					slew-rate = <1>;
					drive-open-drain;
					bias-disable;
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
			sdmmc1_b4_sleep_pins_a: sdmmc1-b4-sleep-0 {
				pins {
					pinmux = <STM32_PINMUX('C', 8, ANALOG)>, /* SDMMC1_D0 */
						 <STM32_PINMUX('C', 9, ANALOG)>, /* SDMMC1_D1 */
						 <STM32_PINMUX('C', 10, ANALOG)>, /* SDMMC1_D2 */
						 <STM32_PINMUX('C', 11, ANALOG)>, /* SDMMC1_D3 */
						 <STM32_PINMUX('C', 12, ANALOG)>, /* SDMMC1_CK */
						 <STM32_PINMUX('D', 2, ANALOG)>; /* SDMMC1_CMD */
				};
			};

			sdmmc1_clk_pins_a: sdmmc1-clk-0 {
				pins {
					pinmux = <STM32_PINMUX('C', 12, AF12)>; /* SDMMC1_CK */
					slew-rate = <1>;
					drive-push-pull;
					bias-pull-up;
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
			fmc_nand_pins: fmc-nand-0 {
				pins1 {
					pinmux = <STM32_PINMUX('D', 14, AF12)>,  /* FMC_D0  */
						 <STM32_PINMUX('D', 15, AF12)>,  /* FMC_D1  */
						 <STM32_PINMUX('D',  0, AF12)>,  /* FMC_D2  */
						 <STM32_PINMUX('D',  1, AF12)>,  /* FMC_D3  */
						 <STM32_PINMUX('E',  7, AF12)>,  /* FMC_D4  */
						 <STM32_PINMUX('E',  8, AF12)>,  /* FMC_D5  */
						 <STM32_PINMUX('E',  9, AF12)>,  /* FMC_D6  */
						 <STM32_PINMUX('E', 10, AF12)>,  /* FMC_D7  */
						 <STM32_PINMUX('D',  4, AF12)>,  /* FMC_NOE */
						 <STM32_PINMUX('D',  5, AF12)>,  /* FMC_NWE */
						 <STM32_PINMUX('D', 11, AF12)>,  /* FMC_CLE */
						 <STM32_PINMUX('D', 12, AF12)>,  /* FMC_ALE */
						 <STM32_PINMUX('G',  9, AF12)>;  /* FMC_NCE */
					bias-disable;
					drive-push-pull;
					slew-rate = <3>;
				};
				pins2 {
					pinmux = <STM32_PINMUX('A', 9, AF10)>;   /* FMC_NWAIT */
					bias-disable;                              /* external 10k pull-up */
				};
			};

			spi5_pins_a: spi5-0 {
				pins1 {
					pinmux = <STM32_PINMUX('H', 7, AF6)>, /* SPI5_SCK */
						 <STM32_PINMUX('H', 3, AF5)>; /* SPI5_MOSI */
					bias-disable;
					drive-push-pull;
					slew-rate = <1>;
				};

				pins2 {
					pinmux = <STM32_PINMUX('A', 8, AF5)>; /* SPI5_MISO */
					bias-disable;
				};
			};

			spi5_sleep_pins_a: spi5-sleep-0 {
				pins {
					pinmux = <STM32_PINMUX('H', 7, ANALOG)>, /* SPI5_SCK */
						 <STM32_PINMUX('A', 8, ANALOG)>, /* SPI5_MISO */
						 <STM32_PINMUX('H', 3, ANALOG)>; /* SPI5_MOSI */
				};
			};

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
			uart8_pins_a: uart8-0 {
				pins1 {
					pinmux = <STM32_PINMUX('E', 1, AF8)>; /* UART8_TX */
					bias-disable;
					drive-push-pull;
					slew-rate = <0>;
				};
				pins2 {
					pinmux = <STM32_PINMUX('F', 9, AF8)>; /* UART8_RX */
					bias-pull-up;
				};
			};

			uart8_idle_pins_a: uart8-idle-0 {
				pins1 {
					pinmux = <STM32_PINMUX('E', 1, ANALOG)>; /* UART8_TX */
				};
				pins2 {
					pinmux = <STM32_PINMUX('F', 9, AF8)>; /* UART8_RX */
					bias-pull-up;
				};
			};

			uart8_sleep_pins_a: uart8-sleep-0 {
				pins {
					pinmux = <STM32_PINMUX('E', 1, ANALOG)>, /* UART8_TX */
						 <STM32_PINMUX('F', 9, ANALOG)>; /* UART8_RX */
				};
			};

			usart1_pins_a: usart1-0 {
				pins1 {
					pinmux = <STM32_PINMUX('C', 0, AF7)>, /* USART1_TX */
						 <STM32_PINMUX('C', 2, AF7)>; /* USART1_RTS */
					bias-disable;
					drive-push-pull;
					slew-rate = <0>;
				};
				pins2 {
					pinmux = <STM32_PINMUX('B', 0, AF4)>, /* USART1_RX */
						 <STM32_PINMUX('A', 7, AF7)>; /* USART1_CTS_NSS */
					bias-pull-up;
				};
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
			usart1_idle_pins_a: usart1-idle-0 {
				pins1 {
					pinmux = <STM32_PINMUX('C', 0, ANALOG)>, /* USART1_TX */
						 <STM32_PINMUX('A', 7, ANALOG)>; /* USART1_CTS_NSS */
				};
				pins2 {
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					slew-rate = <0>;
				};
				pins3 {
					pinmux = <STM32_PINMUX('B', 0, AF4)>; /* USART1_RX */
					bias-pull-up;
				};
			};

			usart1_sleep_pins_a: usart1-sleep-0 {
				pins {
					pinmux = <STM32_PINMUX('C', 0, ANALOG)>, /* USART1_TX */
						 <STM32_PINMUX('C', 2, ANALOG)>, /* USART1_RTS */
						 <STM32_PINMUX('A', 7, ANALOG)>, /* USART1_CTS_NSS */
						 <STM32_PINMUX('B', 0, ANALOG)>; /* USART1_RX */
				};
			};

			usart2_pins_a: usart2-0 {
				pins1 {
					pinmux = <STM32_PINMUX('H', 12, AF1)>, /* USART2_TX */
						 <STM32_PINMUX('D', 4, AF3)>; /* USART2_RTS */
					bias-disable;
					drive-push-pull;
					slew-rate = <0>;
				};
				pins2 {
					pinmux = <STM32_PINMUX('D', 15, AF1)>, /* USART2_RX */
						 <STM32_PINMUX('E', 11, AF2)>; /* USART2_CTS_NSS */
					bias-disable;
				};
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
			usart2_idle_pins_a: usart2-idle-0 {
				pins1 {
					pinmux = <STM32_PINMUX('H', 12, ANALOG)>, /* USART2_TX */
						 <STM32_PINMUX('E', 11, ANALOG)>; /* USART2_CTS_NSS */
				};
				pins2 {
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					slew-rate = <0>;
				};
				pins3 {
					pinmux = <STM32_PINMUX('D', 15, AF1)>; /* USART2_RX */
					bias-disable;
				};
			};

			usart2_sleep_pins_a: usart2-sleep-0 {
				pins {
					pinmux = <STM32_PINMUX('H', 12, ANALOG)>, /* USART2_TX */
						 <STM32_PINMUX('D', 4, ANALOG)>, /* USART2_RTS */
						 <STM32_PINMUX('D', 15, ANALOG)>, /* USART2_RX */
						 <STM32_PINMUX('E', 11, ANALOG)>; /* USART2_CTS_NSS */
				};
			};
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
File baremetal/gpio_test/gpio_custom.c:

// SPDX-License-Identifier: BSD-3-Clause
// Copyright (c) 2026 Jakob Kastelic
//
// Custom-board GPIO connectivity sweep. The SRS STM32MP135 PCB routes 22
// SPI/QUADSPI signals out of header J503; each is wired to a ball on
// the iCE40-HX8K-B-EVN. This firmware drives one of those MP135 pins at a
// time so the FPGA sampler (which holds every sampled ball at its weak
// internal pull-up) can report which ball changed: an input reads 1 unless
// actively driven, so driving a pin LOW makes exactly its wired ball read 0,
// and that single zero bit identifies the connection.
//
// Built only for BOARD_CUSTOM; under EVB this is an empty translation unit so
// the eval-board mission keeps the original gpio_replay_mpu_stub.c behaviour.

#ifdef BOARD_CUSTOM

#include <stddef.h>
#include <stdint.h>

#include "console.h"
#include "gpio_custom.h"
#include "printf.h"
#include "stm32mp13xx_hal.h"
#include "stm32mp13xx_hal_gpio.h"
#include "stm32mp13xx_hal_rcc.h"

typedef struct {
   const char   *name;
   GPIO_TypeDef *port;
   uint16_t      pin;
} custom_signal_t;

// Order is the discovery index sent over UART (two hex digits). Pin map
// extracted from kicad Rev_B mpu_dsp_fpga.kicad_sch (net label -> primary
// STM32MP135 pin name, e.g. "PE2/SPI5_MOSI").
static const custom_signal_t custom_signals[] = {
   {"QUADSPI_CLK", GPIOF, GPIO_PIN_10},
   {"QUADSPI_CS",  GPIOE, GPIO_PIN_14},
   {"QUADSPI_IO0", GPIOF, GPIO_PIN_8},
   {"QUADSPI_IO1", GPIOF, GPIO_PIN_9},
   {"QUADSPI_IO2", GPIOD, GPIO_PIN_7},
   {"QUADSPI_IO3", GPIOH, GPIO_PIN_7},
   {"SPI1_SCK",    GPIOB, GPIO_PIN_1},
   {"SPI1_MOSI",   GPIOA, GPIO_PIN_3},
   {"SPI1_MISO",   GPIOC, GPIO_PIN_3},
   {"SPI1_CS",     GPIOF, GPIO_PIN_12},
   {"SPI2_SCK",    GPIOH, GPIO_PIN_6},
   {"SPI2_MOSI",   GPIOH, GPIO_PIN_10},
   {"SPI2_MISO",   GPIOG, GPIO_PIN_1},
   {"SPI2_CS",     GPIOB, GPIO_PIN_13},
   {"SPI4_SCK",    GPIOB, GPIO_PIN_4},
   {"SPI4_MOSI",   GPIOE, GPIO_PIN_11},
   {"SPI4_MISO",   GPIOE, GPIO_PIN_13},
   {"SPI4_CS",     GPIOD, GPIO_PIN_10},
   {"SPI5_SCK",    GPIOG, GPIO_PIN_10},
   {"SPI5_MOSI",   GPIOE, GPIO_PIN_2},
   {"SPI5_MISO",   GPIOG, GPIO_PIN_8},
   {"SPI5_CS",     GPIOH, GPIO_PIN_11},
};
#define CUSTOM_SIGNAL_COUNT (sizeof(custom_signals) / sizeof(custom_signals[0]))

static void custom_enable_gpio_clocks(void)
{
   __HAL_RCC_GPIOA_CLK_ENABLE();
   __HAL_RCC_GPIOB_CLK_ENABLE();
   __HAL_RCC_GPIOC_CLK_ENABLE();
   __HAL_RCC_GPIOD_CLK_ENABLE();
   __HAL_RCC_GPIOE_CLK_ENABLE();
   __HAL_RCC_GPIOF_CLK_ENABLE();
   __HAL_RCC_GPIOG_CLK_ENABLE();
   __HAL_RCC_GPIOH_CLK_ENABLE();
}

static void custom_config_input(const custom_signal_t *s)
{
   GPIO_InitTypeDef g = {
      .Pin   = s->pin,
      .Mode  = GPIO_MODE_INPUT,
      .Pull  = GPIO_NOPULL,
      .Speed = GPIO_SPEED_FREQ_LOW,
   };
   HAL_GPIO_Init(s->port, &g);
}

static void custom_config_output(const custom_signal_t *s)
{
   GPIO_InitTypeDef g = {
      .Pin   = s->pin,
      .Mode  = GPIO_MODE_OUTPUT_PP,
      .Pull  = GPIO_NOPULL,
      .Speed = GPIO_SPEED_FREQ_LOW,
   };
   HAL_GPIO_Init(s->port, &g);
}

static void custom_release_all(void)
{
   for (size_t i = 0; i < CUSTOM_SIGNAL_COUNT; i++)
      custom_config_input(&custom_signals[i]);
   my_printf("gpio_test release all ok\r\n");
}

static void custom_drive(size_t idx, int high)
{
   const custom_signal_t *s = &custom_signals[idx];
   custom_config_output(s);
   HAL_GPIO_WritePin(s->port, s->pin, high ? GPIO_PIN_SET : GPIO_PIN_RESET);
   my_printf("gpio_test drive %s %s ok\r\n", s->name, high ? "high" : "low");
}

static int hexval(char c)
{
   if (c >= '0' && c <= '9')
      return c - '0';
   if (c >= 'a' && c <= 'f')
      return c - 'a' + 10;
   if (c >= 'A' && c <= 'F')
      return c - 'A' + 10;
   return -1;
}

// Command protocol (one command per UART write, no terminator needed):
//   D<nn><L|H>  drive signal index nn (two hex digits) low/high, push-pull
//   R           release every signal back to high-impedance input
// A bad hex digit or out-of-range index aborts the in-flight command.
void gpio_custom_run(void)
{
   enum { IDLE, WANT_D1, WANT_D0, WANT_LEVEL } st = IDLE;
   int d1 = 0, d0 = 0;

   custom_enable_gpio_clocks();
   custom_release_all();
   my_printf("gpio_test custom ready\r\n");

   for (;;) {
      while (!console_rx_empty()) {
         char c = console_rx_get();

         switch (st) {
         case IDLE:
            if (c == 'D')
               st = WANT_D1;
            else if (c == 'R')
               custom_release_all();
            break;
         case WANT_D1:
            d1 = hexval(c);
            st = (d1 < 0) ? IDLE : WANT_D0;
            break;
         case WANT_D0:
            d0 = hexval(c);
            st = (d0 < 0) ? IDLE : WANT_LEVEL;
            break;
         case WANT_LEVEL: {
            size_t idx = (size_t)(d1 * 16 + d0);
            if (idx < CUSTOM_SIGNAL_COUNT) {
               if (c == 'H')
                  custom_drive(idx, 1);
               else if (c == 'L')
                  custom_drive(idx, 0);
            }
            st = IDLE;
            break;
         }
         }
      }
   }
}

#endif /* BOARD_CUSTOM */

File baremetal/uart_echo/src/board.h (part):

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#define DDR_DX1DQTR  0xffffffff
#define DDR_DX1DQSTR 0x3db02001

#define CTP_INT_PORT    GPIOF
#define CTP_INT_PIN     GPIO_PIN_5
#define CTP_SCL_PORT    GPIOD
#define CTP_SCL_PIN     GPIO_PIN_1
#define CTP_SDA_PORT    GPIOH
#define CTP_SDA_PIN     GPIO_PIN_6
#define CTP_AF          GPIO_AF4_I2C5
#define CTP_RST_PORT    GPIOH
#define CTP_RST_PIN     GPIO_PIN_2
#define CTP_INT_IRQn    EXTI5_IRQn
#define CTP_INT_PIN_NUM 5U
#define ctp_irqhandler  EXTI5_IRQHandler
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#define ETH_RX_CLK_PORT GPIOA
#define ETH_RX_CLK_PIN  GPIO_PIN_1
#define ETH_RX_CLK_AF   GPIO_AF11_ETH
#define ETH_MDIO_PORT   GPIOA
#define ETH_MDIO_PIN    GPIO_PIN_2
#define ETH_MDIO_AF     GPIO_AF11_ETH
#define ETH_TX_EN_PORT  GPIOB
#define ETH_TX_EN_PIN   GPIO_PIN_11
#define ETH_TX_EN_AF    GPIO_AF11_ETH
#define ETH_CRS_DV_PORT GPIOC
#define ETH_CRS_DV_PIN  GPIO_PIN_1
#define ETH_CRS_DV_AF   GPIO_AF10_ETH
#define ETH_RXD0_PORT   GPIOC
#define ETH_RXD0_PIN    GPIO_PIN_4
#define ETH_RXD0_AF     GPIO_AF11_ETH
#define ETH_RXD1_PORT   GPIOC
#define ETH_RXD1_PIN    GPIO_PIN_5
#define ETH_RXD1_AF     GPIO_AF11_ETH
#define ETH_MDC_PORT    GPIOG
#define ETH_MDC_PIN     GPIO_PIN_2
#define ETH_MDC_AF      GPIO_AF11_ETH
#define ETH_TXD0_PORT   GPIOG
#define ETH_TXD0_PIN    GPIO_PIN_13
#define ETH_TXD0_AF     GPIO_AF11_ETH
#define ETH_TXD1_PORT   GPIOG
#define ETH_TXD1_PIN    GPIO_PIN_14
#define ETH_TXD1_AF     GPIO_AF11_ETH
#define ETH_NRST_PIN    MCP_PIN_9

#define FMC_MAKER             0x00U
#define FMC_DEV               0x00U
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#define DDR_DX1DQTR     0xffffffff
#define DDR_DX1DQSTR    0x3db02001

#define CTP_INT_PORT    GPIOH
#define CTP_INT_PIN     GPIO_PIN_12
#define CTP_SCL_PORT    GPIOH
#define CTP_SCL_PIN     GPIO_PIN_13
#define CTP_SDA_PORT    GPIOF
#define CTP_SDA_PIN     GPIO_PIN_3
#define CTP_AF          GPIO_AF4_I2C5
#define CTP_RST_PORT    GPIOB
#define CTP_RST_PIN     GPIO_PIN_7
#define CTP_INT_IRQn    EXTI12_IRQn
#define CTP_INT_PIN_NUM 12U
#define ctp_irqhandler  EXTI12_IRQHandler
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#undef ETH_RX_CLK_PORT
#undef ETH_RX_CLK_PIN
#undef ETH_RX_CLK_AF
#define ETH_CLK_PORT      GPIOA
#define ETH_CLK_PIN       GPIO_PIN_11
#define ETH_CLK_AF        GPIO_AF11_ETH
#define ETH_MDIO_PORT     GPIOG
#define ETH_MDIO_PIN      GPIO_PIN_3
#define ETH_MDIO_AF       GPIO_AF11_ETH
#define ETH_TX_EN_PORT    GPIOB
#define ETH_TX_EN_PIN     GPIO_PIN_11
#define ETH_TX_EN_AF      GPIO_AF11_ETH
#define ETH_CRS_DV_PORT   GPIOA
#define ETH_CRS_DV_PIN    GPIO_PIN_7
#define ETH_CRS_DV_AF     GPIO_AF11_ETH
#define ETH_RXD0_PORT     GPIOC
#define ETH_RXD0_PIN      GPIO_PIN_4
#define ETH_RXD0_AF       GPIO_AF11_ETH
#define ETH_RXD1_PORT     GPIOC
#define ETH_RXD1_PIN      GPIO_PIN_5
#define ETH_RXD1_AF       GPIO_AF11_ETH
#define ETH_MDC_PORT      GPIOG
#define ETH_MDC_PIN       GPIO_PIN_2
#define ETH_MDC_AF        GPIO_AF11_ETH
#define ETH_TXD0_PORT     GPIOG
#define ETH_TXD0_PIN      GPIO_PIN_13
#define ETH_TXD0_AF       GPIO_AF11_ETH
#define ETH_TXD1_PORT     GPIOG
#define ETH_TXD1_PIN      GPIO_PIN_14
#define ETH_TXD1_AF       GPIO_AF11_ETH
#define ETH_PHY_INTN_PORT GPIOG
#define ETH_PHY_INTN_PIN  GPIO_PIN_12
#define ETH_PHY_INTN_AF   GPIO_AF11_ETH
#define ETH_NRST_PORT     GPIOG
#define ETH_NRST_PIN      GPIO_PIN_11

#define FMC_MAKER             0xC2U
#define FMC_DEV               0xDCU
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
